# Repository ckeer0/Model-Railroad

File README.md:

# Model-Railroad
All code and files for the Model Railroad

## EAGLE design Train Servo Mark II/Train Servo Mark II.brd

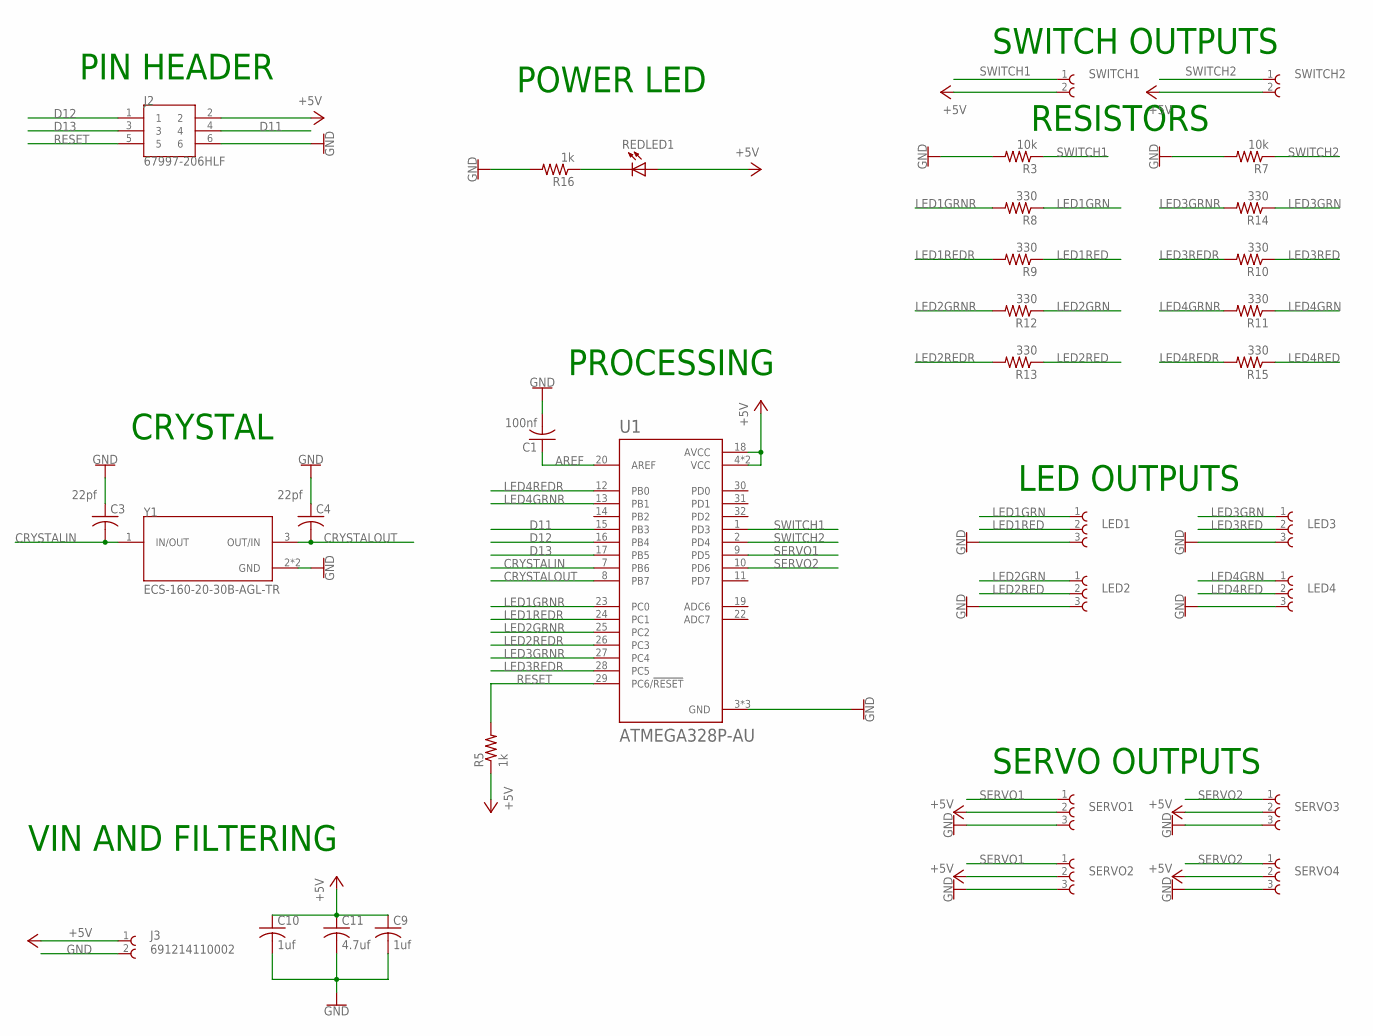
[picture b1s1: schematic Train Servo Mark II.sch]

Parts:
C1: 100nf; C0805
C3, C4: 22pf; C0805
C9, C10: 1uf; C0805
C11: 4.7uf; C1206K
J2: 67997-206HLF; FRAMATOME_67997-206HLF
J3: 691214110002
LED1, LED2, LED3, LED4: 691214110003
R3, R7: 10k; M0805
R5, R16: 1k; M0805
R8, R9, R10, R11, R12, R13, R14, R15: 330; M0805
REDLED1: LTST-C171KGKT; DIOC200X125X110
SERVO1, SERVO2, SERVO3, SERVO4: 691214110003
SWITCH1, SWITCH2: 691214110002
U1: ATMEGA328P-AU; QFP80P900X900X120-32N
Y1: ECS-160-20-30B-AGL-TR; XTAL_ECS-160-20-30B-AGL-TR

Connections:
+5V: C9.1, C10.1, C11.1, J2.2, J3.1, R5.1, REDLED1.+, SERVO1.2, SERVO2.2, SERVO3.2, SERVO4.2, SWITCH1.2, SWITCH2.2, U1.4 (VCC), U1.6 (VCC), U1.18 (AVCC)
AREF: C1.1, U1.20 (AREF)
CRYSTALIN: C3.2, U1.7 (PB6), Y1.1 (IN/OUT)
CRYSTALOUT: C4.2, U1.8 (PB7), Y1.3 (OUT/IN)
D11: J2.4, U1.15 (PB3)
D12: J2.1, U1.16 (PB4)
D13: J2.3, U1.17 (PB5)
GND: C1.2, C3.1, C4.1, C9.2, C10.2, C11.2, J2.6, J3.2, LED1.3, LED2.3, LED3.3, LED4.3, R3.2, R7.2, R16.2, SERVO1.3, SERVO2.3, SERVO3.3, SERVO4.3, U1.3 (GND), U1.5 (GND), U1.21 (GND), Y1.2 (GND), Y1.4 (GND)
LED1GRN: LED1.1, R8.1
LED1GRNR: R8.2, U1.23 (PC0)
LED1RED: LED1.2, R9.1
LED1REDR: R9.2, U1.24 (PC1)
LED2GRN: LED2.1, R12.1
LED2GRNR: R12.2, U1.25 (PC2)
LED2RED: LED2.2, R13.1
LED2REDR: R13.2, U1.26 (PC3)
LED3GRN: LED3.1, R14.1
LED3GRNR: R14.2, U1.27 (PC4)
LED3RED: LED3.2, R10.1
LED3REDR: R10.2, U1.28 (PC5)
LED4GRN: LED4.1, R11.1
LED4GRNR: R11.2, U1.13 (PB1)
LED4RED: LED4.2, R15.1
LED4REDR: R15.2, U1.12 (PB0)
unnamed: R16.1, REDLED1.-
RESET: J2.5, R5.2, U1.29 (PC6/!RESET)
SERVO1: SERVO1.1, SERVO2.1, U1.9 (PD5)
SERVO2: SERVO3.1, SERVO4.1, U1.10 (PD6)
SWITCH1: R3.1, SWITCH1.1, U1.1 (PD3)
SWITCH2: R7.1, SWITCH2.1, U1.2 (PD4)

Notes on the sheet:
CRYSTAL
VIN AND FILTERING
PIN HEADER
PROCESSING
SERVO OUTPUTS
LED OUTPUTS
SWITCH OUTPUTS
RESISTORS
POWER LED

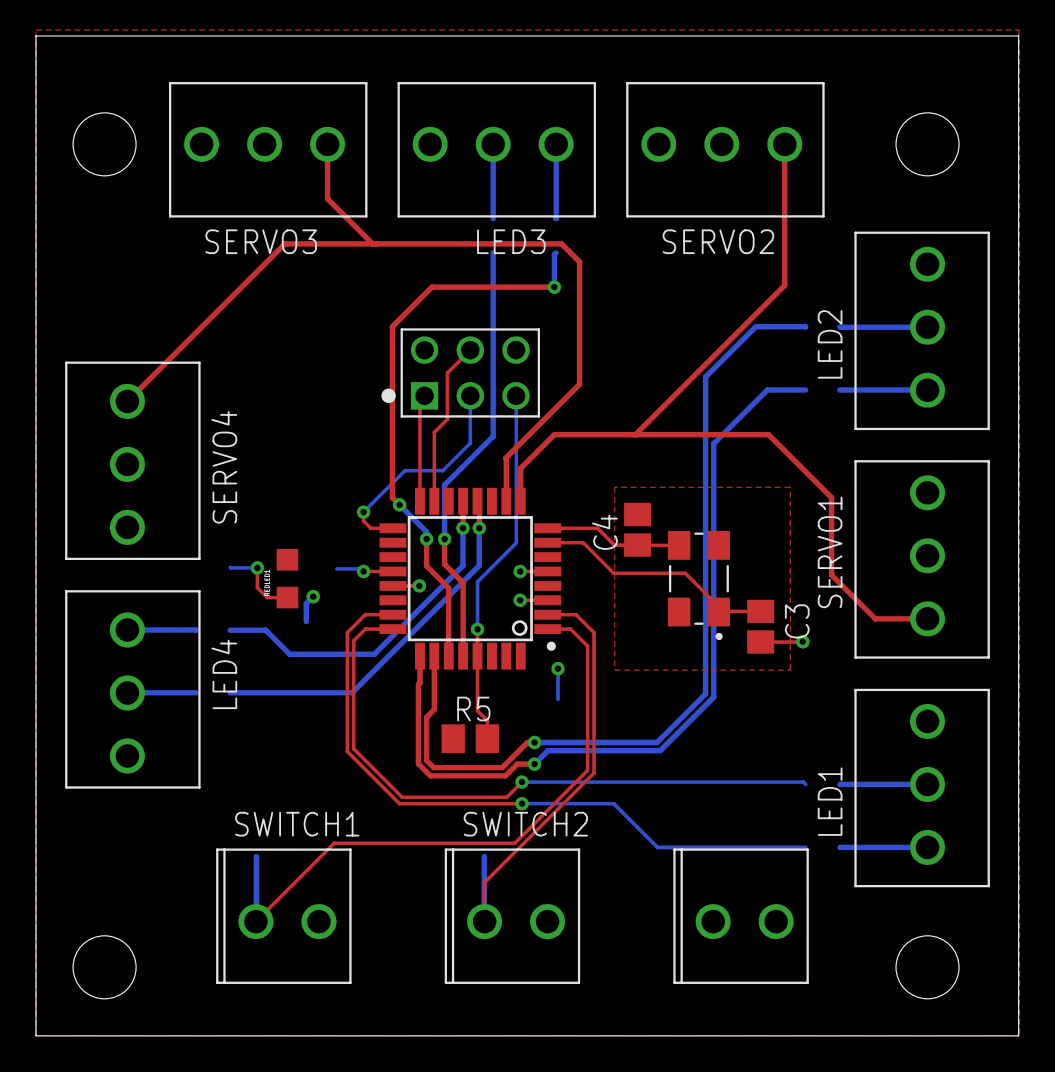
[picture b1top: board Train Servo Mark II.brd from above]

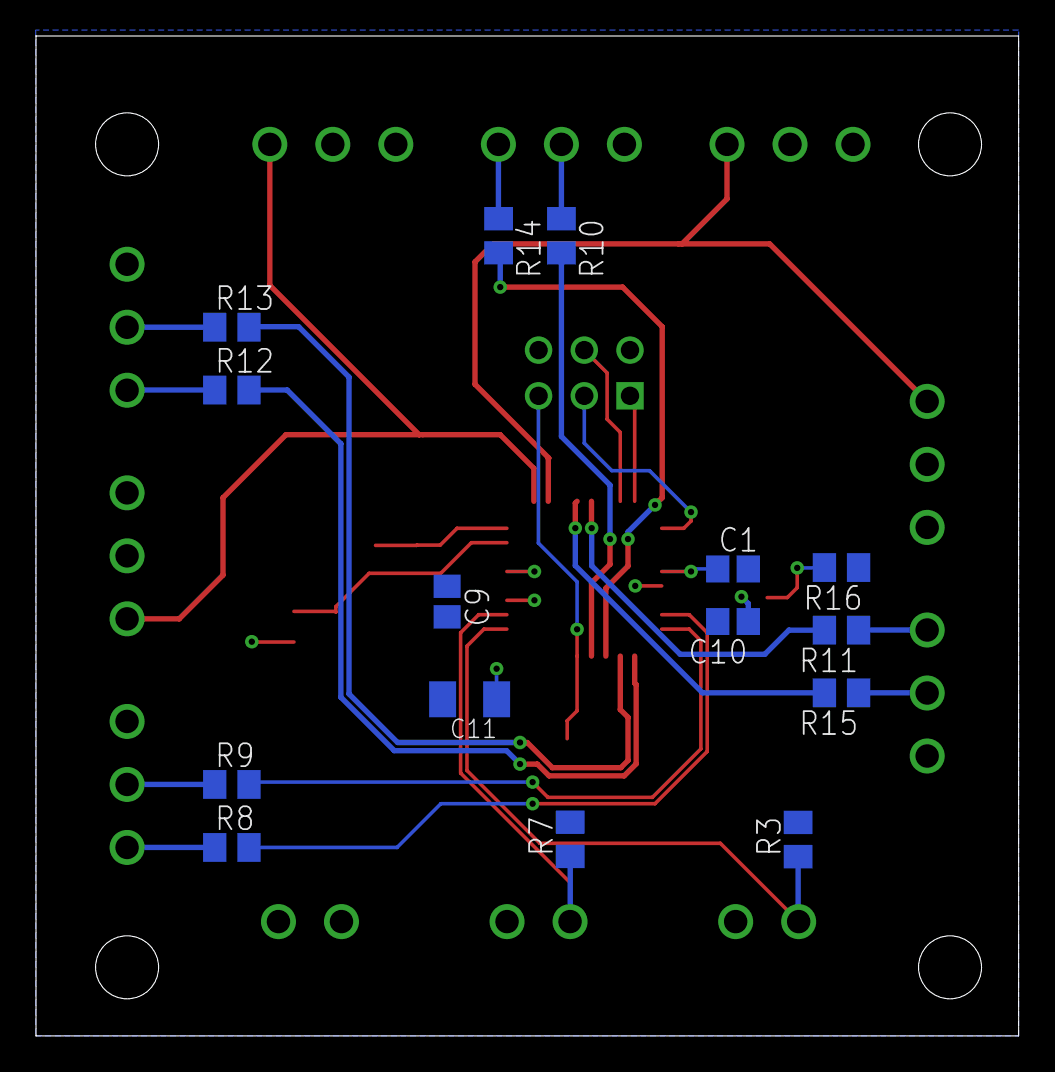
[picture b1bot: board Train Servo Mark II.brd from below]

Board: 2 copper layers, 54.6 x 55.5 mm, 33 parts (15 on the bottom side), 30 nets.

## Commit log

2020-05-27 Initial Upload of Mk II files

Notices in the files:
parts and their libraries:
SparkFun-PowerSymbols: Licensing: Creative Commons ShareAlike 4.0 International - https://creativecommons.org/licenses/by-sa/4.0
